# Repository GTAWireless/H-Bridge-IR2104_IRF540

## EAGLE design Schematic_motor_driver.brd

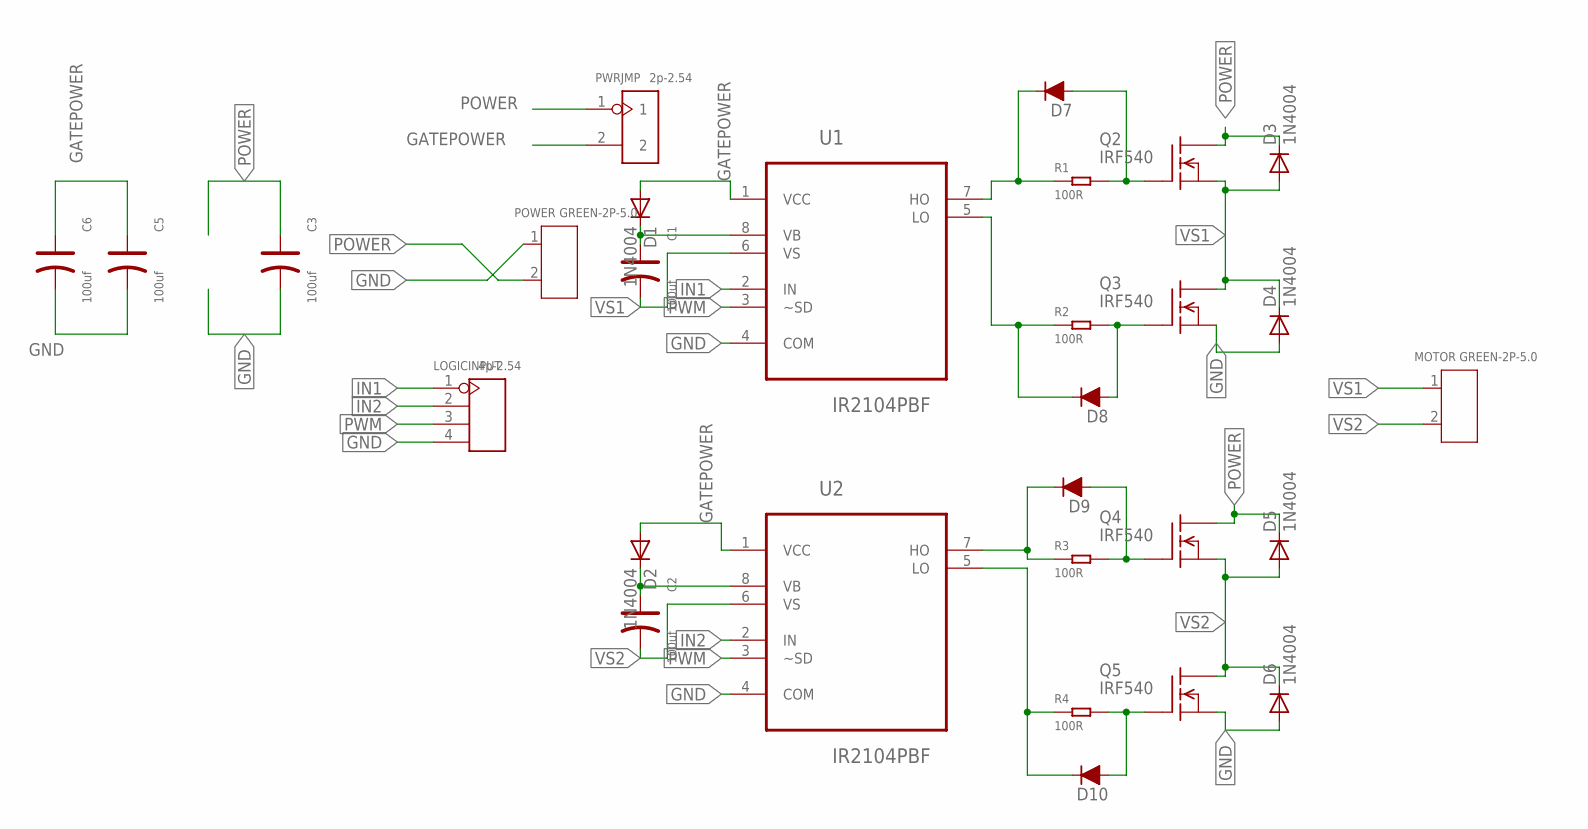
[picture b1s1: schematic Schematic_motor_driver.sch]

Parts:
C1, C2, C3, C5, C6: 100uf; PC-D5.3MM
D1, D2, D3, D4, D5, D6: 1N4004; DO41-10
D7, D8, D9, D10: D-FILL-MLL-41; MELF-MLL41
LOGICINPUT: 4p-2.54; H4-2.54
MOTOR: GREEN-2P-5.0; H2-5.0-10.5X8.0MM
POWER: GREEN-2P-5.0; H2-5.0-10.5X8.0MM
PWRJMP: 2p-2.54; H2-2.54
Q2, Q3, Q4, Q5: IRF540; TO220
R1, R2, R3, R4: 100R; R1206
U1, U2: IR2104PBF; DIP254P762X533-8

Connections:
GATEPOWER: C5.+, C6.+, D1.A, D2.A, PWRJMP.2, U1.1 (VCC), U2.1 (VCC)
GND: C3.-, C5.-, C6.-, D4.A, D6.A, LOGICINPUT.4, POWER.1, Q3.3 (S), Q5.3 (S), U1.4 (COM), U2.4 (COM)
IN1: LOGICINPUT.1, U1.2 (IN)
IN2: LOGICINPUT.2, U2.2 (IN)
unnamed: D8.2 (A), Q3.1 (G), R2.2
unnamed: C1.+, D1.C, U1.8 (VB)
unnamed: D9.2 (A), Q4.1 (G), R3.2
unnamed: C2.+, D2.C, U2.8 (VB)
unnamed: D10.2 (A), Q5.1 (G), R4.2
unnamed: D7.2 (A), Q2.1 (G), R1.2
unnamed: D7.1 (C), R1.1, U1.7 (HO)
unnamed: D8.1 (C), R2.1, U1.5 (LO)
unnamed: D9.1 (C), R3.1, U2.7 (HO)
unnamed: D10.1 (C), R4.1, U2.5 (LO)
POWER: C3.+, D3.C, D5.C, POWER.2, PWRJMP.1, Q2.2 (D), Q4.2 (D)
PWM: LOGICINPUT.3, U1.3 (~SD), U2.3 (~SD)
VS1: C1.-, D3.A, D4.C, MOTOR.1, Q2.3 (S), Q3.2 (D), U1.6 (VS)
VS2: C2.-, D5.A, D6.C, MOTOR.2, Q4.3 (S), Q5.2 (D), U2.6 (VS)

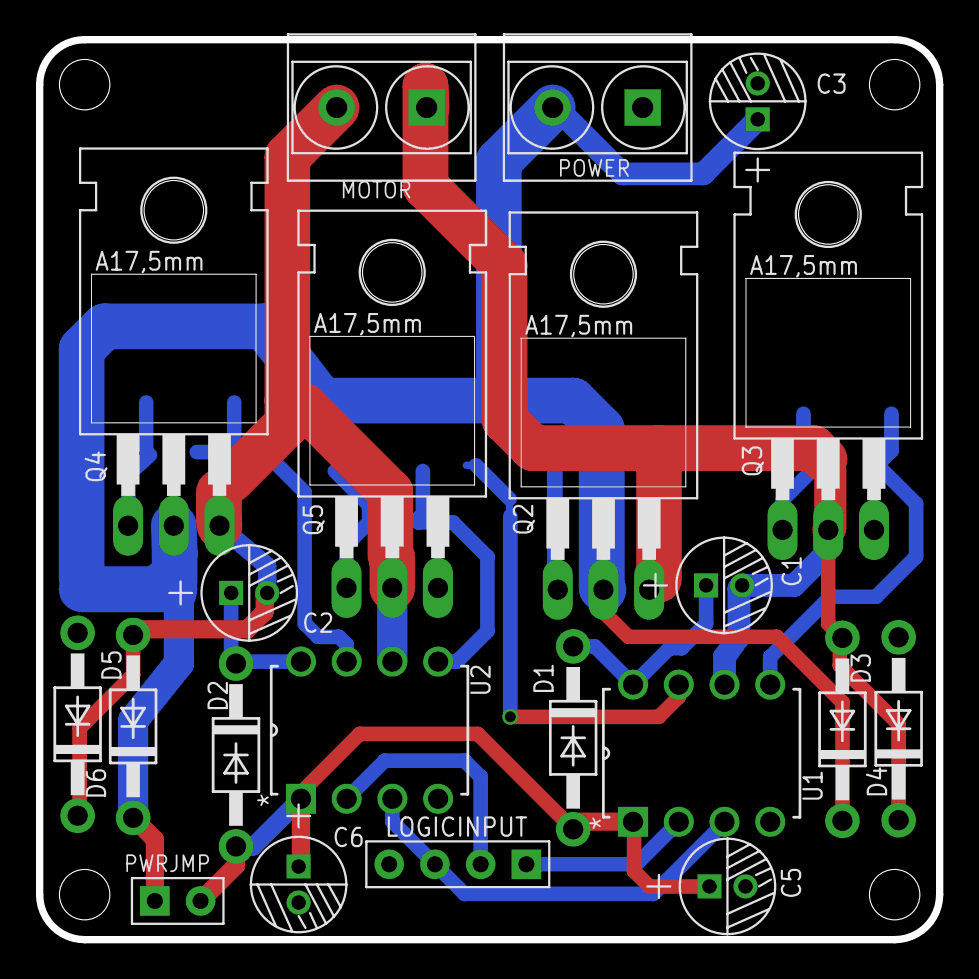
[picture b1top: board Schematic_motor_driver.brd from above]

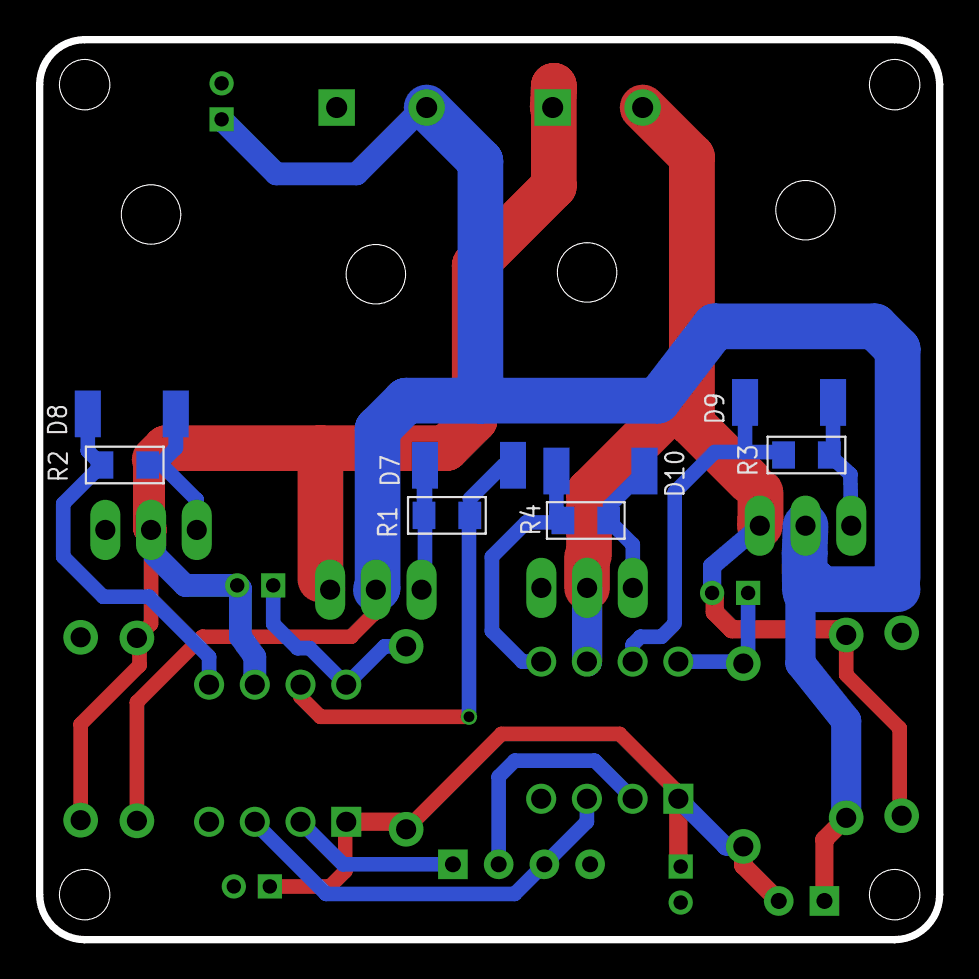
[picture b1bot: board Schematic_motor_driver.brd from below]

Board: 2 copper layers, 50.0 x 50.0 mm, 29 parts (8 on the bottom side), 18 nets.

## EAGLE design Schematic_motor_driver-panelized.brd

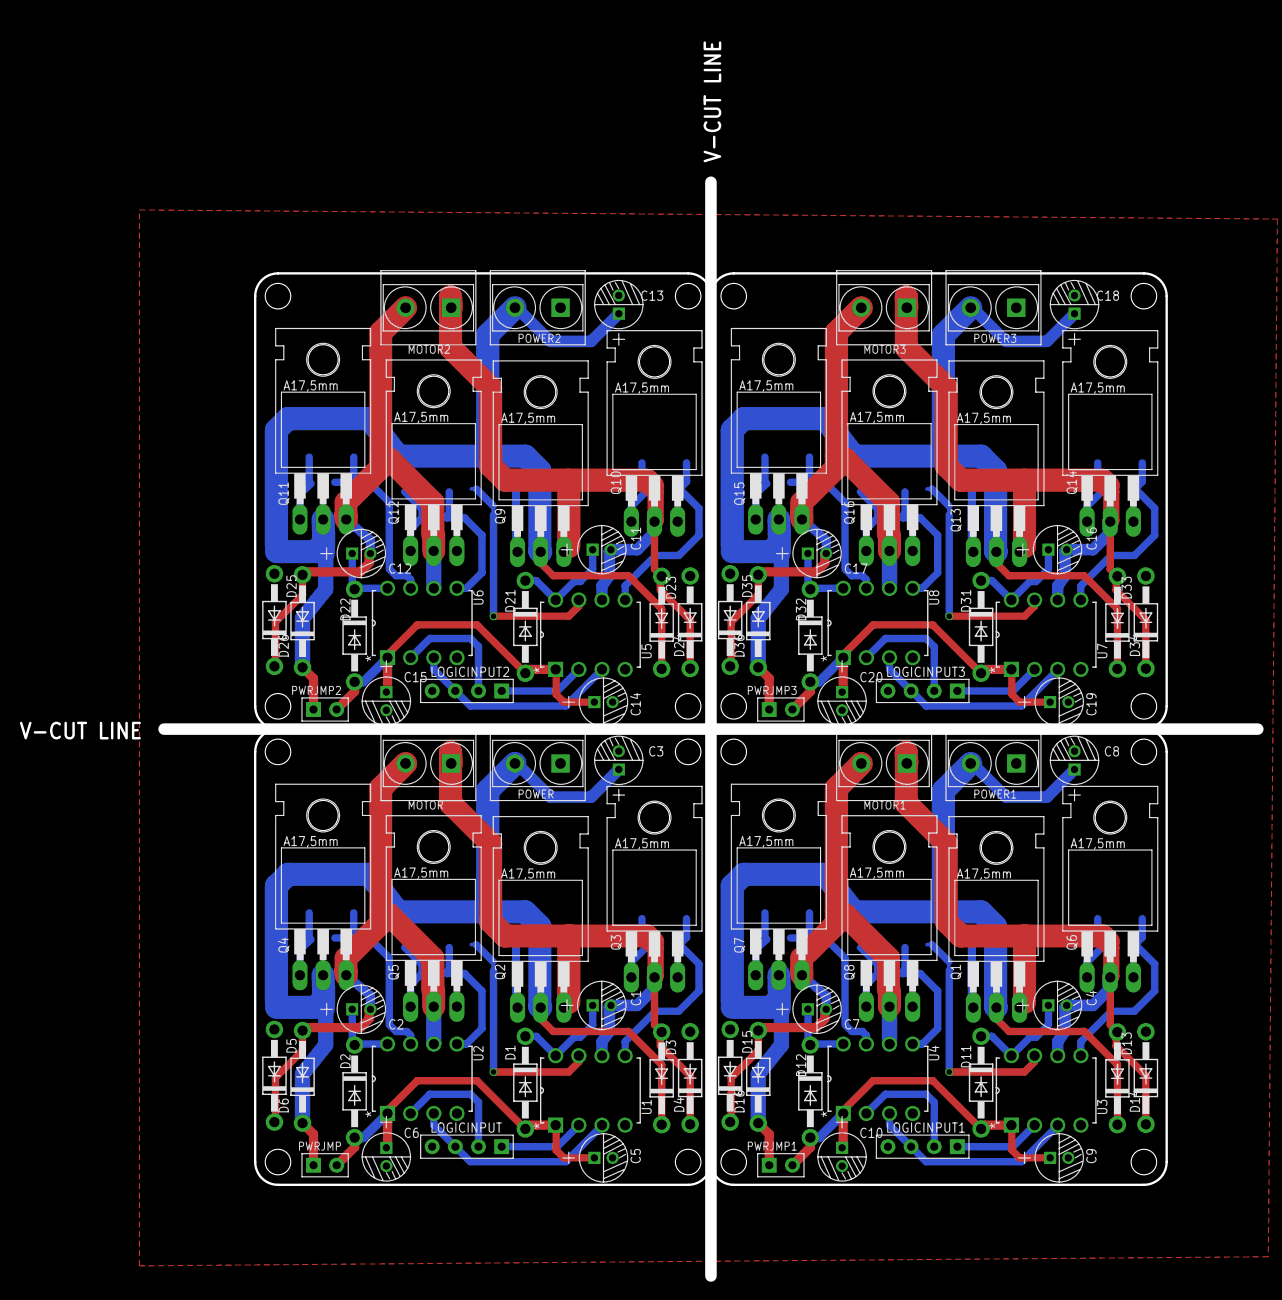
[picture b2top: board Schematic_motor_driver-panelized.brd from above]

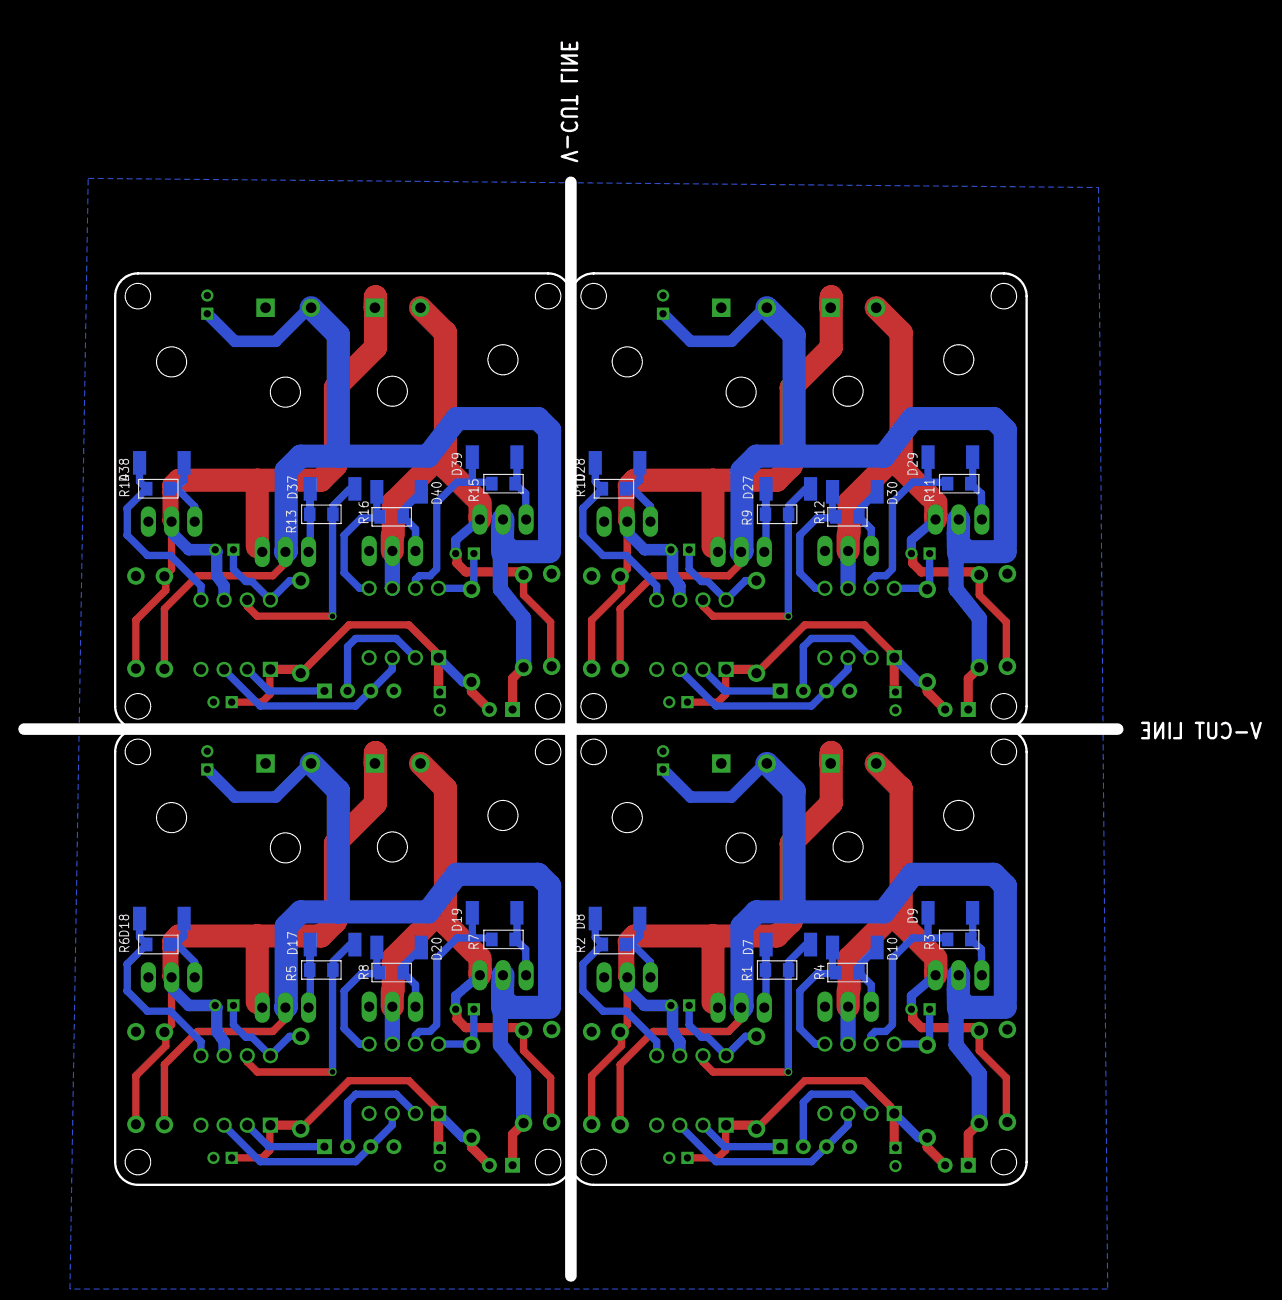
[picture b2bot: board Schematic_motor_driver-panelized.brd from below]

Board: 2 copper layers, 135.4 x 137.4 mm, 116 parts (32 on the bottom side), 69 nets.

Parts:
C1, C2, C3, C4, C5, C6, C7, C8, C9, C10, C11, C12, C13, C14, C15, C16, C17, C18, C19, C20: 100uf; PC-D5.3MM
D1, D2, D3, D4, D5, D6, D11, D12, D13, D14, D15, D16, D21, D22, D23, D24, D25, D26, D31, D32, D33, D34, D35, D36: 1N4004; DO41-10
D7, D8, D9, D10, D17, D18, D19, D20, D27, D28, D29, D30, D37, D38, D39, D40: MELF-MLL41
LOGICINPUT, LOGICINPUT1, LOGICINPUT2, LOGICINPUT3: 4p-2.54; H4-2.54
MOTOR, MOTOR1, MOTOR2, MOTOR3: GREEN-2P-5.0; H2-5.0-10.5X8.0MM
POWER, POWER1, POWER2, POWER3: GREEN-2P-5.0; H2-5.0-10.5X8.0MM
PWRJMP, PWRJMP1, PWRJMP2, PWRJMP3: 2p-2.54; H2-2.54
Q1, Q2, Q3, Q4, Q5, Q6, Q7, Q8, Q9, Q10, Q11, Q12, Q13, Q14, Q15, Q16: IRF540; TO220
R1, R2, R3, R4, R5, R6, R7, R8, R9, R10, R11, R12, R13, R14, R15, R16: 100R; R1206
U1, U2, U3, U4, U5, U6, U7, U8: IR2104PBF; DIP254P762X533-8

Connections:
GATEPOWER: C5.+, C6.+, D1.A, D2.A, PWRJMP.2, U1.1, U2.1
GATEPOWER1: C9.+, C10.+, D11.A, D12.A, PWRJMP1.2, U3.1, U4.1
GATEPOWER2: C14.+, C15.+, D21.A, D22.A, PWRJMP2.2, U5.1, U6.1
GATEPOWER3: C19.+, C20.+, D31.A, D32.A, PWRJMP3.2, U7.1, U8.1
GND: C3.-, C5.-, C6.-, C8.-, C9.-, C10.-, C13.-, C14.-, C15.-, C18.-, C19.-, C20.-, D4.A, D6.A, D14.A, D16.A, D24.A, D26.A, D34.A, D36.A, LOGICINPUT.4, LOGICINPUT1.4, LOGICINPUT2.4, LOGICINPUT3.4, POWER.1, POWER1.1, POWER2.1, POWER3.1, Q3.3, Q5.3, Q6.3, Q8.3, Q10.3, Q12.3, Q14.3, Q16.3, U1.4, U2.4, U3.4, U4.4, U5.4, U6.4, U7.4, U8.4
IN1: LOGICINPUT.1, U1.2
IN2: LOGICINPUT.2, U2.2
IN3: LOGICINPUT1.1, U3.2
IN4: LOGICINPUT1.2, U4.2
IN5: LOGICINPUT2.1, U5.2
IN6: LOGICINPUT2.2, U6.2
IN7: LOGICINPUT3.1, U7.2
IN8: LOGICINPUT3.2, U8.2
unnamed: D8.2, Q3.1, R2.2
unnamed: C1.+, D1.C, U1.8
unnamed: D9.2, Q4.1, R3.2
unnamed: C2.+, D2.C, U2.8
unnamed: D10.2, Q5.1, R4.2
unnamed: D7.2, Q2.1, R1.2
unnamed: D7.1, R1.1, U1.7
unnamed: D8.1, R2.1, U1.5
unnamed: D9.1, R3.1, U2.7
unnamed: D10.1, R4.1, U2.5
unnamed: C4.+, D11.C, U3.8
unnamed: C7.+, D12.C, U4.8
unnamed: D19.2, Q7.1, R7.2
unnamed: D20.2, Q8.1, R8.2
unnamed: D17.2, Q1.1, R5.2
unnamed: D17.1, R5.1, U3.7
unnamed: D18.1, R6.1, U3.5
unnamed: D19.1, R7.1, U4.7
unnamed: D20.1, R8.1, U4.5
unnamed: D18.2, Q6.1, R6.2
unnamed: C11.+, D21.C, U5.8
unnamed: C12.+, D22.C, U6.8
unnamed: D29.2, Q11.1, R11.2
unnamed: D30.2, Q12.1, R12.2
unnamed: D27.2, Q9.1, R9.2
unnamed: D27.1, R9.1, U5.7
unnamed: D28.1, R10.1, U5.5
unnamed: D29.1, R11.1, U6.7
unnamed: D30.1, R12.1, U6.5
unnamed: D28.2, Q10.1, R10.2
unnamed: C16.+, D31.C, U7.8
unnamed: C17.+, D32.C, U8.8
unnamed: D39.2, Q15.1, R15.2
unnamed: D40.2, Q16.1, R16.2
unnamed: D37.2, Q13.1, R13.2
unnamed: D37.1, R13.1, U7.7
unnamed: D38.1, R14.1, U7.5
unnamed: D39.1, R15.1, U8.7
unnamed: D40.1, R16.1, U8.5
unnamed: D38.2, Q14.1, R14.2
POWER: C3.+, D3.C, D5.C, POWER.2, PWRJMP.1, Q2.2, Q4.2
POWER1: C8.+, D13.C, D15.C, POWER1.2, PWRJMP1.1, Q1.2, Q7.2
POWER2: C13.+, D23.C, D25.C, POWER2.2, PWRJMP2.1, Q9.2, Q11.2
POWER3: C18.+, D33.C, D35.C, POWER3.2, PWRJMP3.1, Q13.2, Q15.2
PWM: LOGICINPUT.3, U1.3, U2.3
PWM1: LOGICINPUT1.3, U3.3, U4.3
PWM2: LOGICINPUT2.3, U5.3, U6.3
PWM3: LOGICINPUT3.3, U7.3, U8.3
VS1: C1.-, D3.A, D4.C, MOTOR.1, Q2.3, Q3.2, U1.6
VS2: C2.-, D5.A, D6.C, MOTOR.2, Q4.3, Q5.2, U2.6
VS3: C4.-, D13.A, D14.C, MOTOR1.1, Q1.3, Q6.2, U3.6
VS4: C7.-, D15.A, D16.C, MOTOR1.2, Q7.3, Q8.2, U4.6
VS5: C11.-, D23.A, D24.C, MOTOR2.1, Q9.3, Q10.2, U5.6
VS6: C12.-, D25.A, D26.C, MOTOR2.2, Q11.3, Q12.2, U6.6
VS7: C16.-, D33.A, D34.C, MOTOR3.1, Q13.3, Q14.2, U7.6
VS8: C17.-, D35.A, D36.C, MOTOR3.2, Q15.3, Q16.2, U8.6

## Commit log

2016-06-23 :tada: Added .gitattributes & .gitignore files
2016-06-23 Mosfet Driver Update1.
    Schematic and board 1st complete
2016-06-24 bridge complete. reviewing
    Thinking Name
2016-06-27 silk adjusted
2016-06-27 PCB Cosmetics
2016-06-28 final reviewed. Completed
2016-06-28 completed 2
2016-06-30 Revert "PCB Cosmetics"
    This reverts commit 40f95e063b70cdd7ef0c66ddfb49b8478f35fe8d.
2016-12-13 adding latest files to git repo
2016-12-14 ready for panelization
2016-12-14 need to fix GND Issues.
2016-12-15 sent to SEEED Fusion - v2
